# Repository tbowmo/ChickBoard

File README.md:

# ChickBoard

A little background info: 
The plan is that all birds in our chicken coop have a RFID tag (using 
125Khz TK4100 tags). Each nest then have an EM4100 RFID reader module,
so I can follow the birds between all nests. 

Because the nests are not placed near each other, I have settled on RS485
for nest communication. It's also planned to have a LED strip or two in the
ceiling, to give a little light in the dark winter nights.

This board is meant as a multipurpose board for this project, so it can be
used in a couple of different situations:

1) RFID reader (EM4100)
2) 1wire bus (can be used with DS1820 to measure temperature)
3) 2 x LED drivers (fet transistors)
4) RS485 bus for communication
5) Atmel ATSAMD20 (upto 256Kb flash)
6) MYSX 2.2 board extension board connector

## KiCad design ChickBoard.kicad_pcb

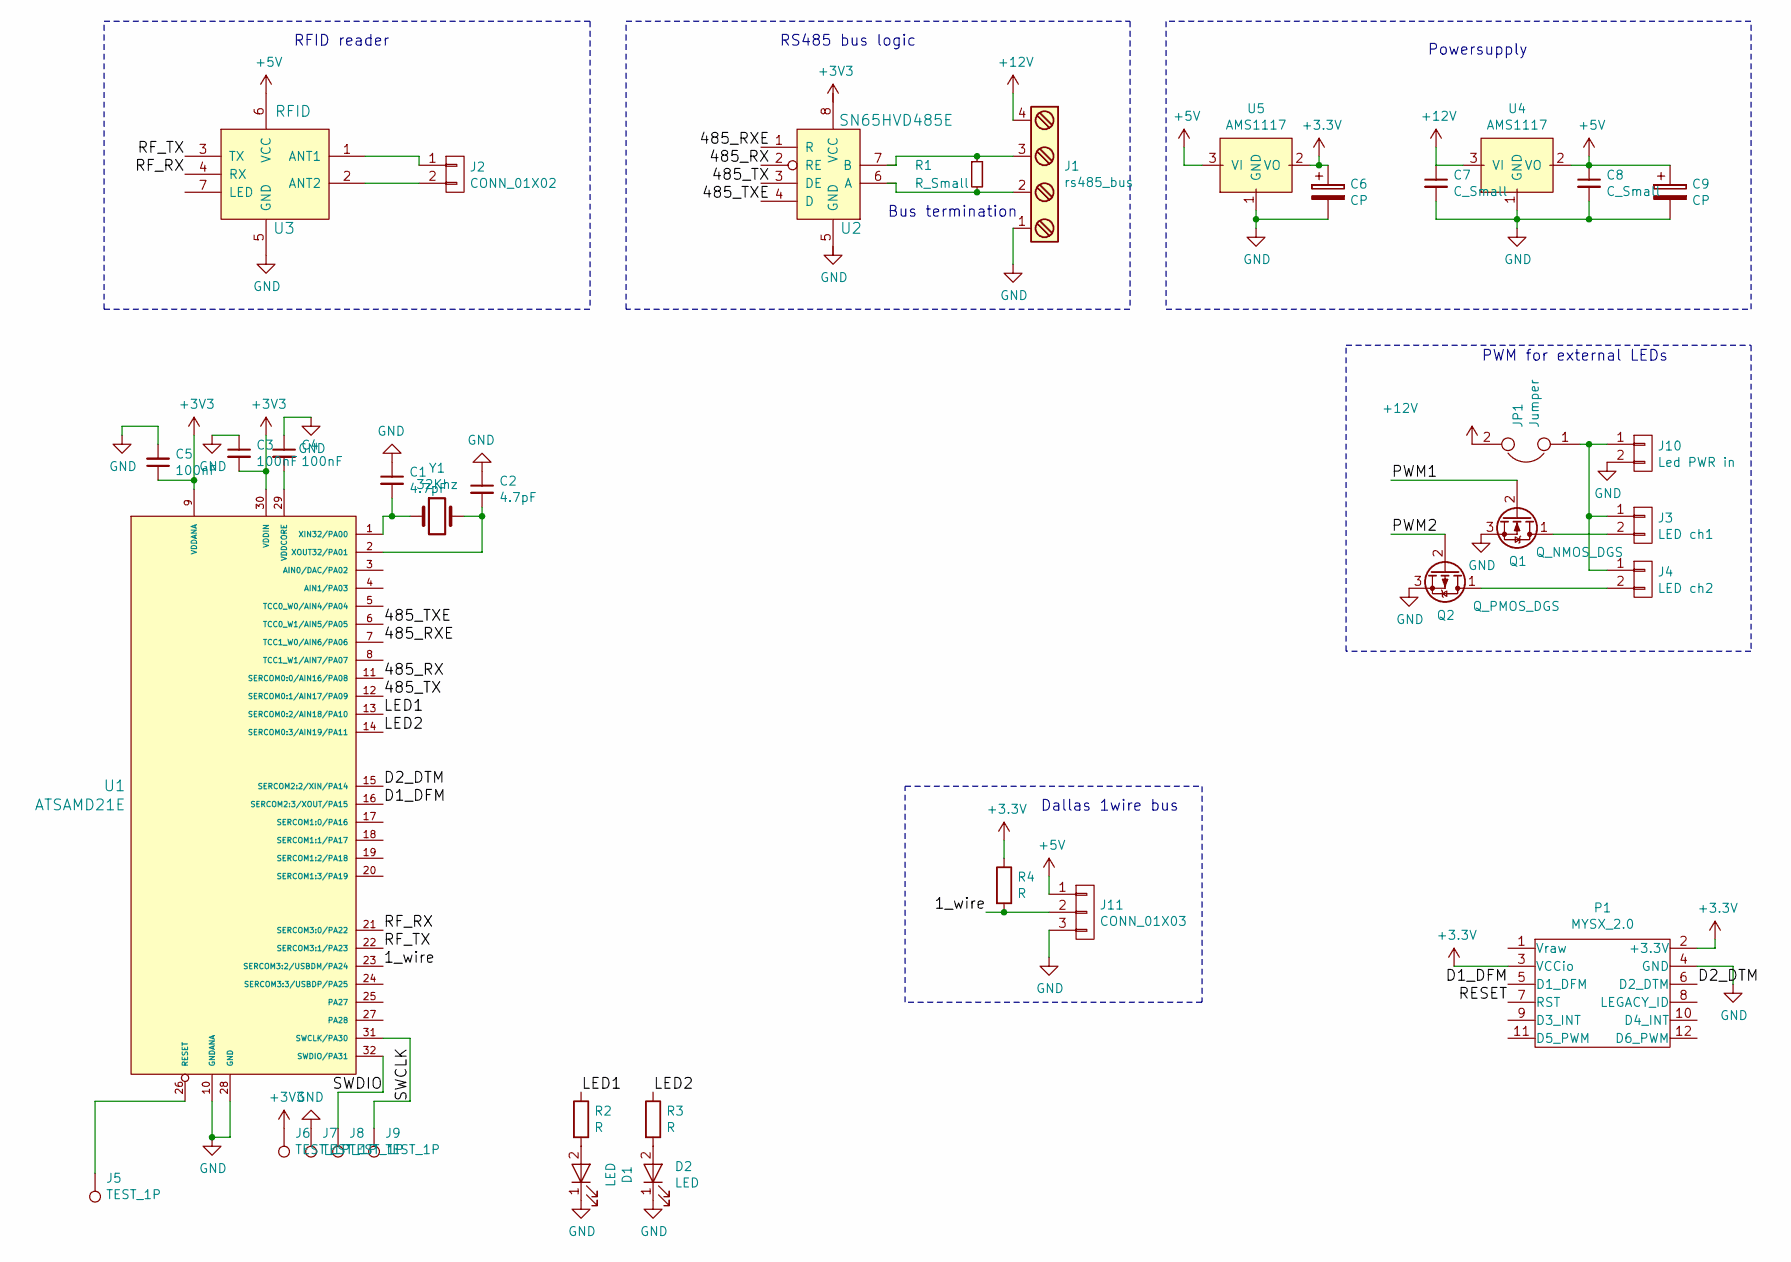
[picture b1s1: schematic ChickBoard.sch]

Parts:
C1, C2: 4.7pF; C_0603_HandSoldering
C3, C4, C5: 100nF; C_0603_HandSoldering
C6, C9: CP; C_0603_HandSoldering
C7, C8: C_Small; C_0603_HandSoldering
D1, D2: LED; LED-0603
J1: rs485_bus; TerminalBlock_Pheonix_MPT-2.54mm_4pol
J2: CONN_01X02; Pin_Header_Straight_1x02
J3: LED ch1; TerminalBlock_Pheonix_MPT-2.54mm_2pol
J4: LED ch2; TerminalBlock_Pheonix_MPT-2.54mm_2pol
J5, J6, J7, J8, J9: TEST_1P; Measurement_Point_Round-SMD-Pad_Small
J10: Led PWR in; TerminalBlock_Pheonix_MPT-2.54mm_2pol
J11: CONN_01X03; TerminalBlock_Pheonix_MPT-2.54mm_3pol
JP1: Jumper; 2_pin_solder_jumper_smd
P1: MYSX_2.0; MYSX_2.2
Q1: Q_NMOS_DGS; SOT-23
Q2: Q_PMOS_DGS; SOT-23
R1: R_Small; R_0603_HandSoldering
R2, R3, R4: R; R_0603_HandSoldering
U1: ATSAMD21E; TQFP-32_7x7mm_Pitch0.8mm
U2: SN65HVD485E; SOIJ-8_5.3x5.3mm_Pitch1.27mm
U3: RFID; EM4100RFID
U4, U5: AMS1117; SOT-23
Y1: 32Khz; XTAL_3.2x1.5mm

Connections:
+5V: C8.1, C9.1, J11.1, U3.6 (VCC), U4.2 (VO), U5.3 (VI)
+12V: C7.1, J1.4, JP1.2, U4.3 (VI)
/1_wire: J11.2, R4.2, U1.23 (SERCOM3:2/USBDM/PA24)
/485_RX: U1.11 (SERCOM0:0/AIN16/PA08), U2.1 (R)
/485_RXE: U1.7 (TCC1_W0/AIN6/PA06), U2.2 (RE)
/485_TX: U1.12 (SERCOM0:1/AIN17/PA09), U2.4 (D)
/485_TXE: U1.6 (TCC0_W1/AIN5/PA05), U2.3 (DE)
/D1_DFM: P1.5 (D1_DFM), U1.16 (SERCOM2:3/XOUT/PA15)
/D2_DTM: P1.6 (D2_DTM), U1.15 (SERCOM2:2/XIN/PA14)
/LED1: R2.1, U1.13 (SERCOM0:2/AIN18/PA10)
/LED2: R3.1, U1.14 (SERCOM0:3/AIN19/PA11)
/PWM1: Q1.2 (G)
/PWM2: Q2.2 (G)
/RESET: P1.7 (RST)
/RF_RX: U1.21 (SERCOM3:0/PA22), U3.4 (RX)
/RF_TX: U1.22 (SERCOM3:1/PA23), U3.3 (TX)
/SWCLK: J9.1, U1.31 (SWCLK/PA30)
/SWDIO: J8.1, U1.32 (SWDIO/PA31)
GND: C1.1, C2.1, C3.1, C4.1, C5.2, C6.2, C7.2, C8.2, C9.2, D1.1 (K), D2.1 (K), J1.1, J7.1, J10.2, J11.3, P1.4 (GND), Q1.3 (S), Q2.3 (S), U1.10 (GNDANA), U1.28 (GND), U2.5 (GND), U3.5 (GND), U4.1 (GND), U5.1 (GND)
unnamed: C1.2, U1.1 (XIN32/PA00), Y1.1
unnamed: C2.2, U1.2 (XOUT32/PA01), Y1.2
unnamed: C4.2, U1.29 (VDDCORE)
unnamed: D1.2 (A), R2.2
unnamed: D2.2 (A), R3.2
unnamed: J1.2, R1.2, U2.6 (A)
unnamed: J1.3, R1.1, U2.7 (B)
unnamed: J2.1, U3.1 (ANT1)
unnamed: J2.2, U3.2 (ANT2)
unnamed: J3.2, Q1.1 (D)
unnamed: J4.2, Q2.1 (D)
unnamed: J5.1, U1.26 (RESET)
unnamed: J3.1, J4.1, J10.1, JP1.1

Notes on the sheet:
Bus termination
Dallas 1wire bus
Powersupply
RS485 bus logic
RFID reader
PWM for external LEDs

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
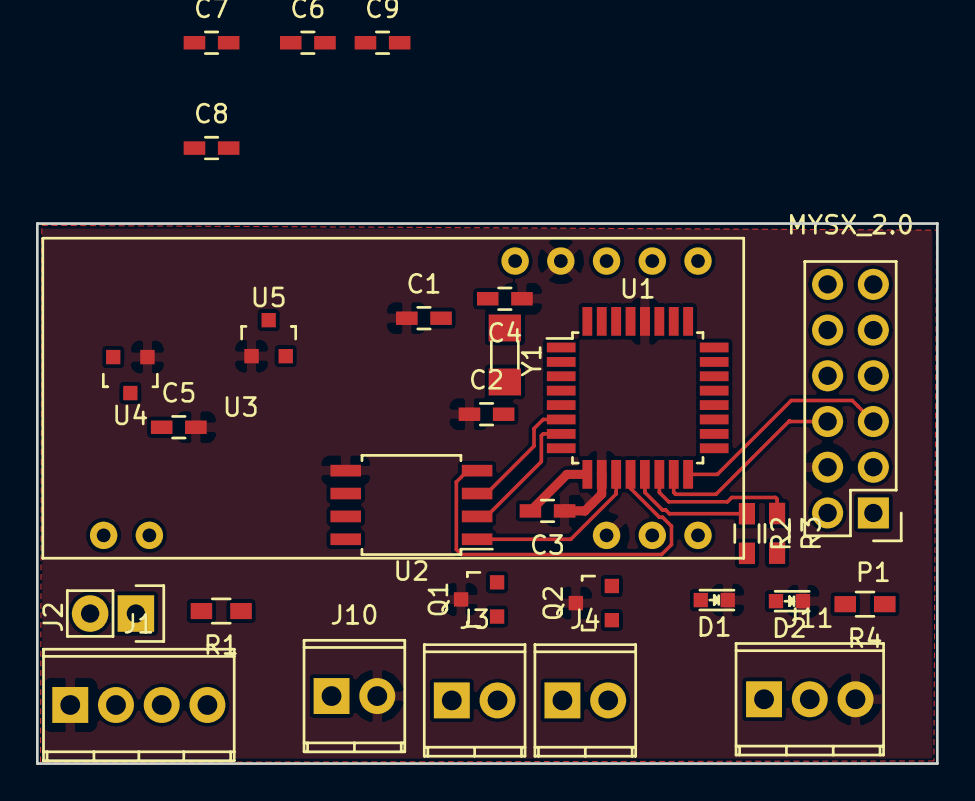
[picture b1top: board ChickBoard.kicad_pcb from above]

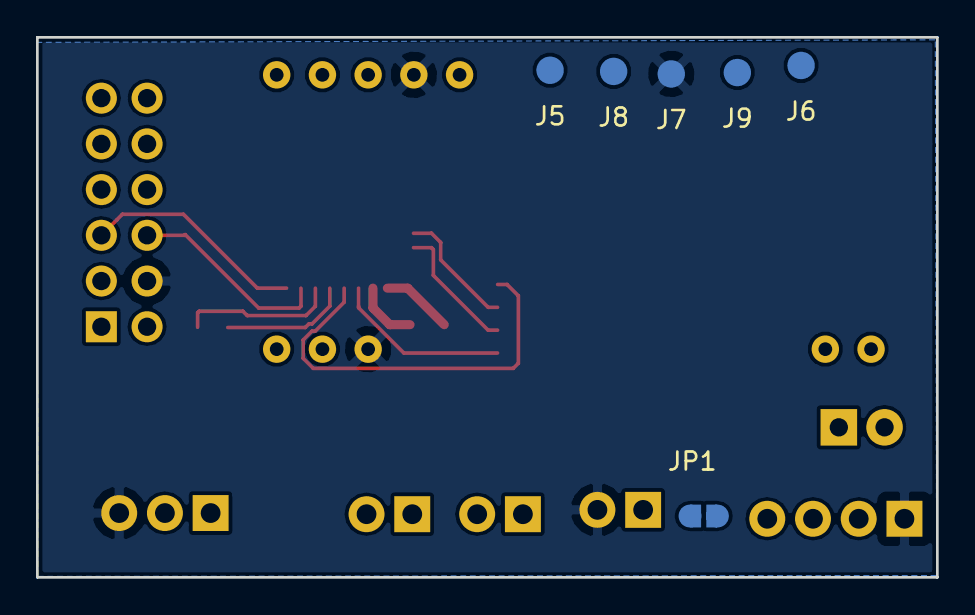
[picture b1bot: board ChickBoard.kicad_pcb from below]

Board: 2 copper layers, 50.0 x 30.0 mm, 36 parts (6 on the bottom side), 30 nets.

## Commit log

2017-08-06 Switched to SAMD20 mcu
2017-08-06 Readme updated
